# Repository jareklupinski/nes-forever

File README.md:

# nes-forever
A Raspberry Pi Hat for controlling the NES sound hardware directly

A work in progress of a circuit that keeps an NES chip in an infinite loop, constantly playing any note data that is shifted into the input registers.

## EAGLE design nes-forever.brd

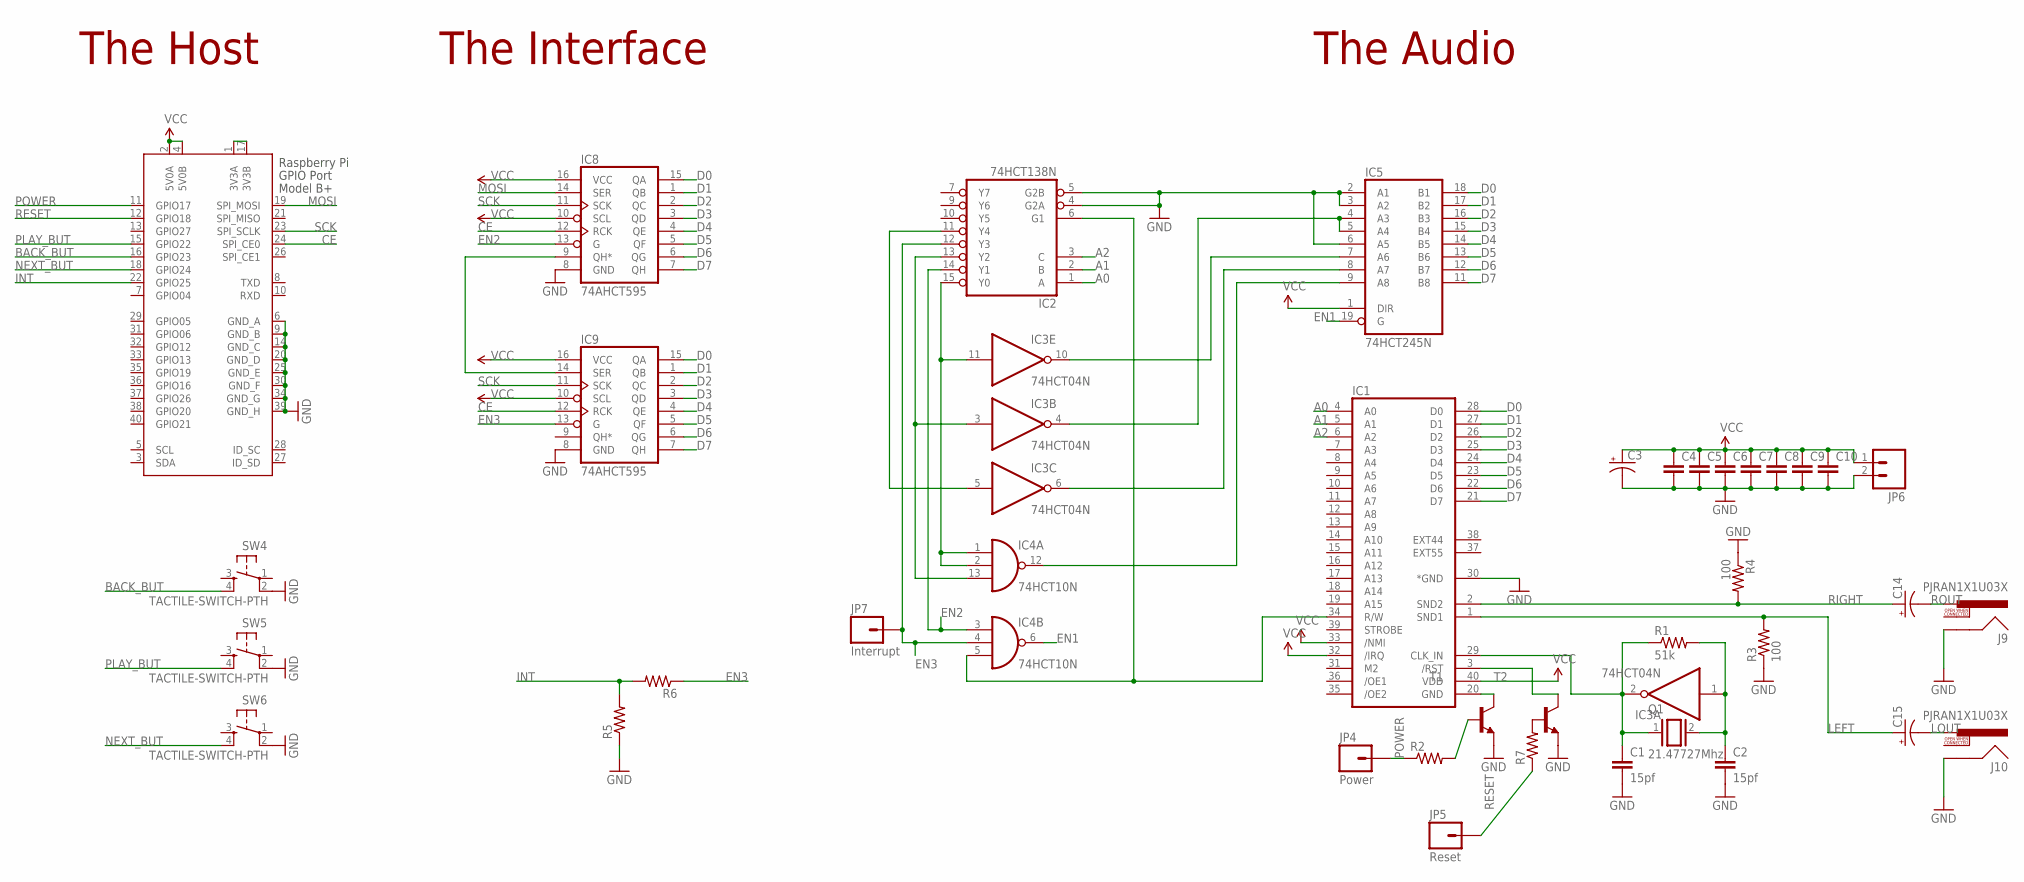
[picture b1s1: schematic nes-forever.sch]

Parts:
C1, C2: 15pf; C025-024X044
C3: CPOL-USE5-8.5; E5-8,5
C4, C5, C6, C7, C8, C9, C10: C-EU025-024X044; C025-024X044
C14, C15: CPOL-USE2-4; E2-4
IC1: 2A03; DIL40
IC2: 74HCT138N; DIL16
IC3: 74HCT04N; DIL14
IC4: 74HCT10N; DIL14
IC5: 74HCT245N; DIL20
IC8, IC9: 74AHCT595; DIL16
J9, J10: PJRAN1X1U03X; RCA
JP4: Power; 1X01
JP5: Reset; 1X01
JP6: M02; 1X02_LONGPADS
JP7: Interrupt; 1X01
Q1: 21.47727Mhz; Q
R1: 51k; 0207/7
R2, R5, R6, R7: R-US_0207/7; 0207/7
R3, R4: 100; 0207/7
SW4, SW5, SW6: TACTILE-SWITCH-PTH; TAC-SWITCH-PTH
T1, T2: 2N2222-NPN-TO92-EBC; TO92-EBC
X2: RASPI_BOARD_B+#_E4; RASPI_BOARD_B+_EDGES_4DRILL

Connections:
3.3V: X2.1 (3V3A), X2.17 (3V3B)
A0: IC1.4 (A0), IC2.1 (A)
A1: IC1.5 (A1), IC2.2 (B)
A2: IC1.6 (A2), IC2.3 (C)
A3: IC3.4 (O), IC5.4 (A3), IC5.5 (A4)
BACK_BUT: SW4.4, X2.16 (GPIO23)
CE: IC8.12 (RCK), IC9.12 (RCK), X2.24 (SPI_CE0)
D0: IC1.28 (D0), IC5.18 (B1), IC8.15 (QA), IC9.15 (QA)
D1: IC1.27 (D1), IC5.17 (B2), IC8.1 (QB), IC9.1 (QB)
D2: IC1.26 (D2), IC5.16 (B3), IC8.2 (QC), IC9.2 (QC)
D3: IC1.25 (D3), IC5.15 (B4), IC8.3 (QD), IC9.3 (QD)
D4: IC1.24 (D4), IC5.14 (B5), IC8.4 (QE), IC9.4 (QE)
D5: IC1.23 (D5), IC5.13 (B6), IC8.5 (QF), IC9.5 (QF)
D6: IC1.22 (D6), IC5.12 (B7), IC8.6 (QG), IC9.6 (QG)
D7: IC1.21 (D7), IC5.11 (B8), IC8.7 (QH), IC9.7 (QH)
EN1: IC4.6 (O), IC5.19 (G)
EN2: IC2.14 (Y1), IC4.3 (I0), IC8.13 (G)
EN3: IC2.12 (Y3), IC4.4 (I1), IC9.13 (G), JP7.1, R6.1
GND: C1.2, C2.2, C3.-, C4.2, C5.2, C6.2, C7.2, C8.2, C9.2, C10.2, IC1.30 (*GND), IC2.4 (G2A), IC2.5 (G2B), IC2.8 (GND), IC3.7 (GND), IC4.7 (GND), IC5.2 (A1), IC5.3 (A2), IC5.6 (A5), IC5.10 (GND), IC8.8 (GND), IC9.8 (GND), J9.SHELL, J10.SHELL, JP6.2, R3.1, R4.1, R5.1, SW4.2, SW5.2, SW6.2, T1.E, T2.E, X2.6 (GND_A), X2.9 (GND_B), X2.14 (GND_C), X2.20 (GND_D), X2.25 (GND_E), X2.30 (GND_F), X2.34 (GND_G), X2.39 (GND_H)
INT: R5.2, R6.2, X2.22 (GPIO25)
LEFT: C15.+, IC1.1 (SND1), R3.2
LOUT: C15.-, J10.PIN
MOSI: IC8.14 (SER), X2.19 (SPI_MOSI)
unnamed: IC3.10 (O), IC5.7 (A6)
unnamed: R7.2, T2.B
unnamed: IC3.6 (O), IC5.8 (A7)
unnamed: IC2.15 (Y0), IC3.11 (I), IC4.1 (I0), IC4.2 (I1)
unnamed: IC4.12 (O), IC5.9 (A8)
unnamed: IC2.13 (Y2), IC3.3 (I), IC4.13 (I2)
unnamed: IC2.11 (Y4), IC3.5 (I)
unnamed: IC1.34 (R/W), IC2.6 (G1), IC4.5 (I2)
unnamed: IC1.20 (GND), T1.C
unnamed: R2.2, T1.B
unnamed: C1.1, IC1.29 (CLK_IN), IC3.2 (O), Q1.1, R1.1
unnamed: C2.1, IC3.1 (I), Q1.2, R1.2
unnamed: IC1.3 (/RST), T2.C
unnamed: IC8.9 (QH*), IC9.14 (SER)
NEXT_BUT: SW6.4, X2.18 (GPIO24)
PLAY_BUT: SW5.4, X2.15 (GPIO22)
POWER: JP4.1, R2.1, X2.11 (GPIO17)
RESET: JP5.1, R7.1, X2.12 (GPIO18)
RIGHT: C14.+, IC1.2 (SND2), R4.2
ROUT: C14.-, J9.PIN
SCK: IC8.11 (SCK), IC9.11 (SCK), X2.23 (SPI_SCLK)
VCC: C3.+, C4.1, C5.1, C6.1, C7.1, C8.1, C9.1, C10.1, IC1.32 (/IRQ), IC1.33 (/NMI), IC1.40 (VDD), IC2.16 (VCC), IC3.14 (VCC), IC4.14 (VCC), IC5.1 (DIR), IC5.20 (VCC), IC8.10 (SCL), IC8.16 (VCC), IC9.10 (SCL), IC9.16 (VCC), JP6.1, X2.2 (5V0A), X2.4 (5V0B)

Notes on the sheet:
The Host
The Interface
The Audio

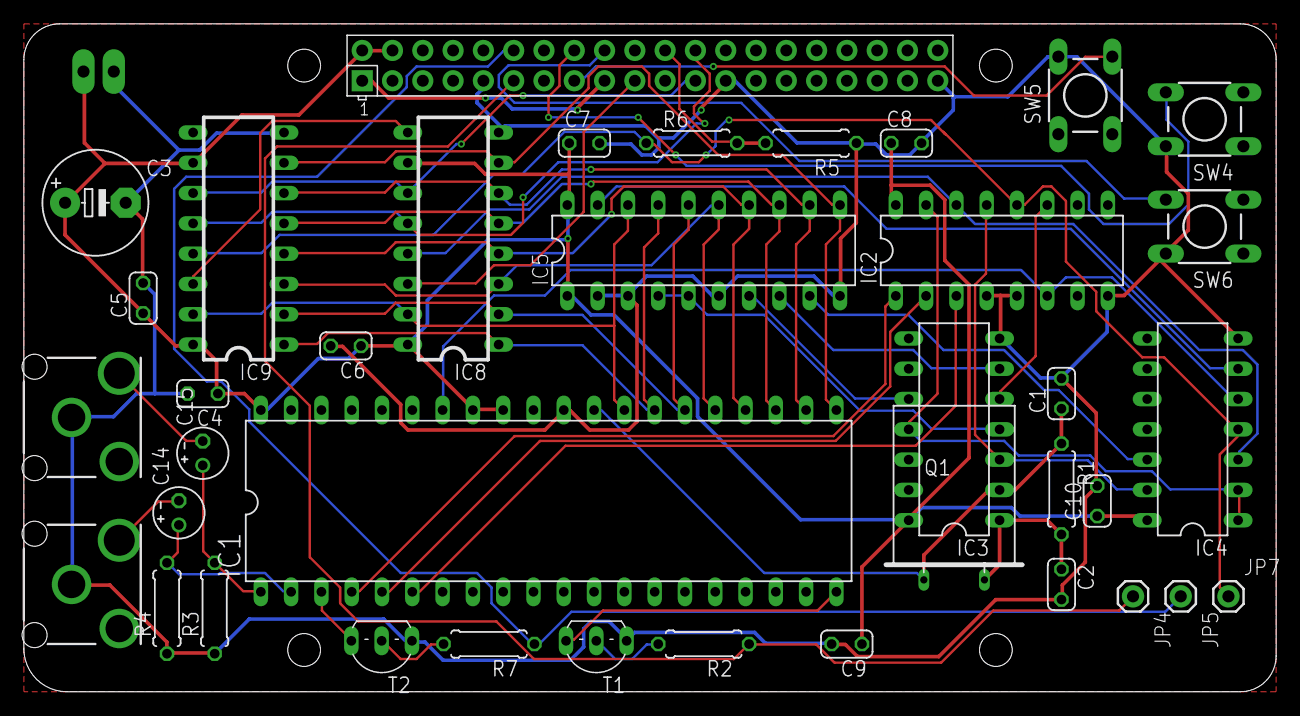
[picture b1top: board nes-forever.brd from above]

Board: 2 copper layers, 105.0 x 56.0 mm, 39 parts (0 on the bottom side), 45 nets.

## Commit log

2018-07-05 design untested

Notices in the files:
parts and their libraries:
SparkFun-Connectors: Licensing: Creative Commons ShareAlike 4.0 International - https://creativecommons.org/licenses/by-sa/4.0
